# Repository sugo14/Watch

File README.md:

This is one of my first major electronics projects (post-CanSat)!

## Project

The goal of this project is to design a custom smartwatch that fits for my personal use case. That includes:

- Shows the time (obviously)
- Maintains a BLE connection with the associated phone
    - Displays notifications
    - Displays current song playing on Spotify
- Has a push-to-talk mic
    - Streams voice notes to the associated phone, for possible analysis later

## Organization

`mc-screen-breakout` has the first revision of the smartwatch PCB, including the MCU module (containing RF stuff asw), a USB-C port, exposed SWD pins, the screen FPC connector, and the microphone.

`watch` **will** contain iterations of the watch PCB that connect to battery and (theoretically) function properly inside the full system, rather than a breakout.

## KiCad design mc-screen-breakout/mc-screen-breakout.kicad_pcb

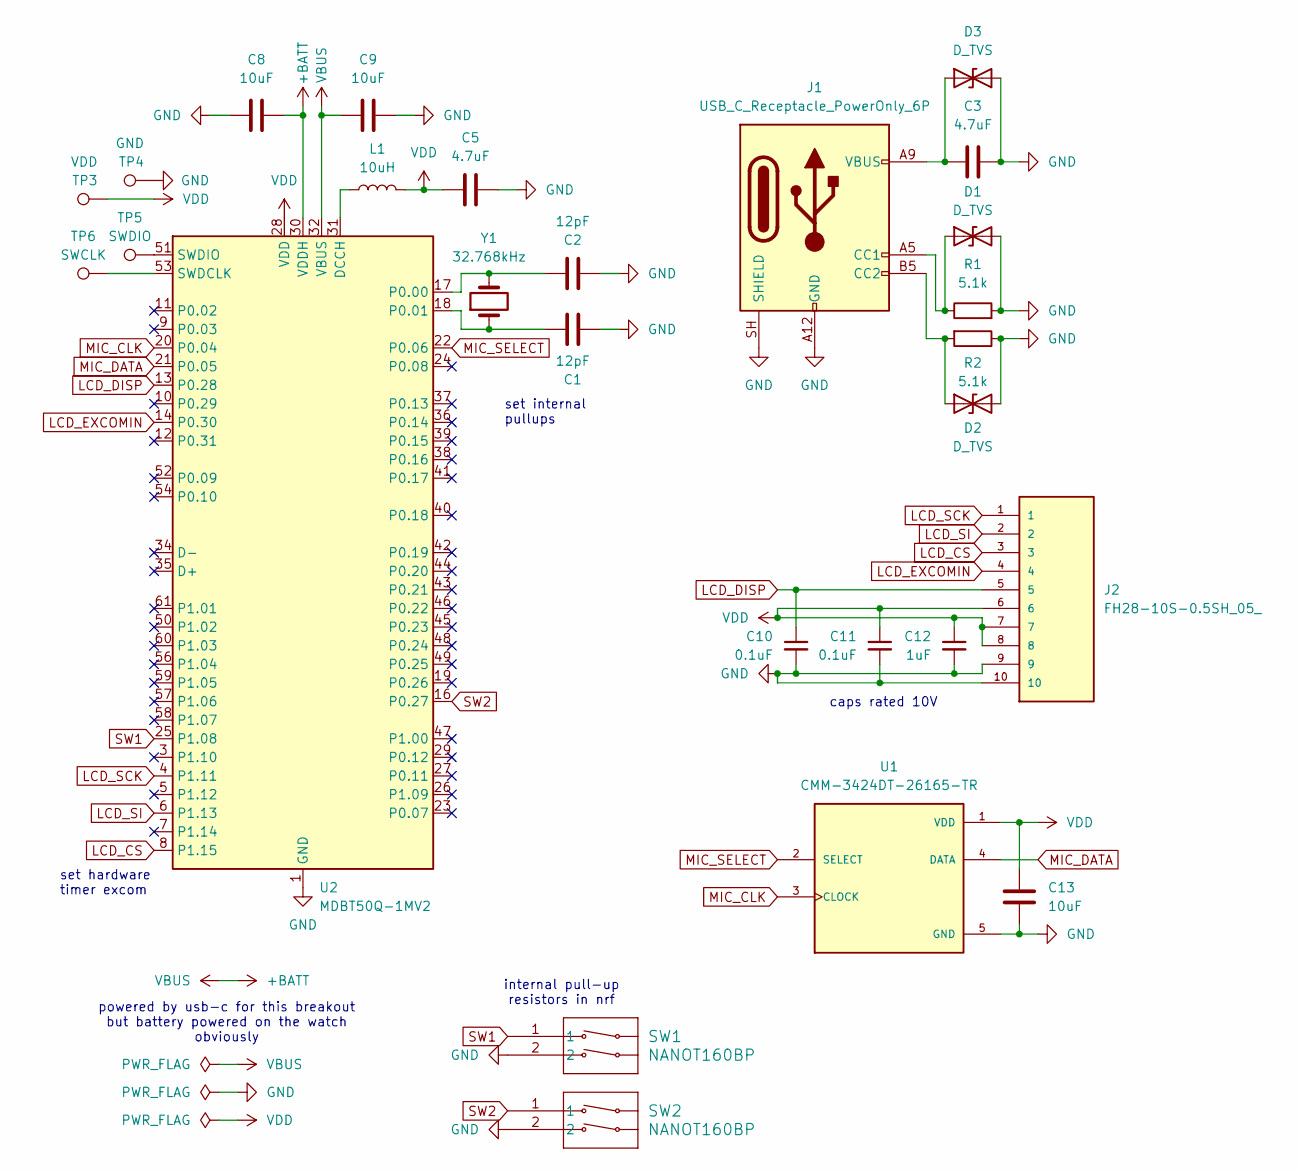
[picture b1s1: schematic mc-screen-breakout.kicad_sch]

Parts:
C1, C2: 12pF; C_0402_1005Metric
C3, C5: 4.7uF; C_0402_1005Metric
C8, C9, C13: 10uF; C_0402_1005Metric
C10, C11: 0.1uF; C_0402_1005Metric
C12: 1uF; C_0402_1005Metric
D1, D2, D3: D_TVS; D_0402_1005Metric
J1: USB_C_Receptacle_PowerOnly_6P; USB_C_Receptacle_Amphenol_124019772112A
J2: FH28-10S-0.5SH_05_; HIROSE_FH28-10S-0.5SH_05_; PARTREV 13.09.20
L1: 10uH; L_0603_1608Metric
R1, R2: 5.1k; R_0402_1005Metric
SW1, SW2: NANOT160BP; Untitled
TP3: VDD; TestPoint_Pad_1.0x1.0mm
TP4: GND; TestPoint_Pad_1.0x1.0mm
TP5: SWDIO; TestPoint_Pad_1.0x1.0mm
TP6: SWCLK; TestPoint_Pad_1.0x1.0mm
U1: CMM-3424DT-26165-TR; MIC_CMM-3424DT-26165-TR; PARTREV 1.0
U2: MDBT50Q-1MV2; Raytac_MDBT50Q
Y1: 32.768kHz; Crystal_SMD_3215-2Pin_3.2x1.5mm

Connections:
+BATT: C8.1, C9.1, U2.30 (VDDH), U2.32 (VBUS)
GND: C1.1, C2.2, C3.2, C5.2, C8.2, C9.2, C10.2, C11.2, C12.2, C13.2, D1.2 (A2), D2.2 (A2), D3.2 (A2), J1.A12 (GND), J1.B12 (GND), J1.SH (SHIELD), J2.9, J2.10, R1.2, R2.1, SW1.2, SW2.2, TP4.1 (1_1), U1.5 (GND), U1.6 (GND), U1.7 (GND), U1.8 (GND), U2.1 (GND), U2.2 (GND), U2.15 (GND), U2.33 (GND), U2.55 (GND)
LCD_CS: J2.3, U2.8 (P1.15)
LCD_DISP: C10.1, J2.5, U2.13 (P0.28)
LCD_EXCOMIN: J2.4, U2.14 (P0.30)
LCD_SCK: J2.1, U2.4 (P1.11)
LCD_SI: J2.2, U2.6 (P1.13)
MIC_CLK: U1.3 (CLOCK), U2.20 (P0.04)
MIC_DATA: U1.4 (DATA), U2.21 (P0.05)
MIC_SELECT: U1.2 (SELECT), U2.22 (P0.06)
unnamed: D1.1 (A1), J1.A5 (CC1), R1.1
unnamed: D2.1 (A1), J1.B5 (CC2), R2.2
unnamed: C3.1, D3.1 (A1), J1.A9 (VBUS), J1.B9 (VBUS)
unnamed: L1.1, U2.31 (DCCH)
unnamed: C2.1, U2.17 (P0.00), Y1.2
unnamed: C1.2, U2.18 (P0.01), Y1.1
unnamed: TP6.1 (1_1), U2.53 (SWDCLK)
unnamed: TP5.1 (1_1), U2.51 (SWDIO)
SW1: SW1.1, U2.25 (P1.08)
SW2: SW2.1, U2.16 (P0.27)
VDD: C5.1, C11.1, C12.1, C13.1, J2.6, J2.7, J2.8, L1.2, TP3.1 (1_1), U1.1 (VDD), U2.28 (VDD)

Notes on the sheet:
powered by usb-c for this breakout but battery powered on the watch obviously
set internal pullups
caps rated 10V
set hardware timer excom
internal pull-up resistors in nrf

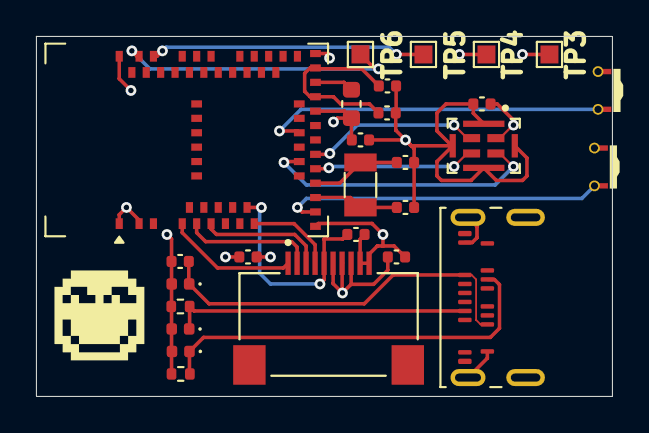
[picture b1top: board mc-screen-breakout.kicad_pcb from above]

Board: 4 copper layers, 32.0 x 20.0 mm, 27 parts (0 on the bottom side), 21 nets.
